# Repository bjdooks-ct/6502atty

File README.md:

# 6502 Atty

A 6502 SBC with an ATMega as a contoller and monitor for the 6502.

This is an initial commit as PCBs are off for manufacture and not been tested. This includes the prototype firmware and the first cut of the firmware code.

The ATmega is probably the easiest MCU to get and program which is 5V tolerant. The 1284P is the current choice as the smaller memory versions are not much cheaper.

There is now a [photo album](https://photos.app.goo.gl/qwDDgCh3WiyMoqd4A) of the build on my google photos.

The clock synchronisation logic is provided by U2A and U2B. U2B takes the PWM output from the ATMega and is used to both halve ti and make it a square wave. The /S input is used when the clock is high to stop any transition low (which would complete the 6502's cycle) which comes from the U2A flip-flop. U2A is triggered by an access to the ATMega and sets /CLOCK_STOP active to stop the 6502 clock until the /AT_ACK signal is active, resetting U2A and making /CLOCK_STOP inactive which then allows U2B to continue generating a clock for the 6502.

## Build notes for v1 rev1

- The 100UF capacitors are 16mm long so trying 47uF, layout change?

The LED resistors will probably need to be reduced to 680R or low as 506R depending on the LEDs being fitted.

The pull-up/pull-down resistors can be anywhere from 1K to 4K7, experiments with previous boards show 10K may not be suitable with certain variants of the 6052. Anything below 1K is probably going to have issues with current dissapation as that will be around 5mA per resistor. 

During test it was found that there seems to be a difference in operation dependong on how the PHi2 jumper is selected. If the PHI2O is used, we get proper operation but if CPU_CLK is seleted then the download code works but the code that is downloaded does not work.

## PCB updates (v1 rev2)

The updates for the second PCB revision are mostly bug-fixes and to make the board smaller to try and get to the 10x10cm point that JLCPCB and others use for cheaper services. There may be in future a version with a few bits of surface mount, like moving to one of the USB capable Atmel devices and adding a direct USB port.

- Added J12 to route ~WE signal to the PGM/~WE to allow SRAM
  - Also requires a R/!W signal gated with PHI2 high
  - Added R~{W}ph signal for ROM
  - This new signal could also drive RAM ~WE and connect ~CS to A15
- Connected ROM's VPP signal to GND, if using SRAM, ties A14 to GND
- U9C's pins 9 and 10 swapped for routing
- U11's E1/E2 pins swapped for easier routing
- Transcription error from prototype, ROM_ACC should be from AND not NAND gate
  - Swao U8C for one of U10 spare gates
- RDY line missing pull-up resistor
- 74LS573 replaced with 74LS574
  - 573 latches when Load is high, and our enable is low
  - 574 will load on rising edge of load pin, so should work
- Made PCB smaller, moved a few LEDs and things around to make this work
- Dropped 1K series drive resistor for the crystal
  - ATMega will not start if this resistor is there
- Serial converter is rotated 180deg to the actual unit
- Recomendation for AVRisp is to use 10K on ATMega's nRESET, so changed for now
  - See crystal series resistor notes.
- Added silkscreen with major part info to help with production

Currently unknown issues:
- Firmware only works with PHI2 jumper on PHI2out
  - can't see any scoped difference between CPUclk and PHI2out
  - possibly a rise-time on the clock with the 1K resistor in it

## PCB updates (v1 rev3)

This revision has minor updates for ease of assembly and a few minor annoyances over how the layout has come out, such as the mounting hole positions not being fully aligned.

The changes are:

- Made LEDs all the same orientation
  - also changed D2's resistor to be on ground side to make routing nicer
- Reduction in the x-size of the board by pushing control logic over
- Changed ROM A13 to solder pad, probably ok to just have A13 on this pin
- Used per-pin options on DIP to remove automatic ground ties
  - manually added a single ground tie to those pads
  - also made the keep-out a bit bigger to allow easier isolation cuts
- Made hole positions mostly consistent at edge of board
- Got down to 100x100mm dimensions with a more shuffling
- Added header and resistors for last two LEDs on bargrapth
  - Hesader J13 and two resistors to VCC for these
- Replaced input buffer U5 with 74x574
  - Added IOCLK from PHI2
  - Removed R26 as not needed
- could we use a 74x574 as input buffer too
  - if we tied ~OE and CP this would almost work, FF loaded on low-high
  - decided to bring PHI2 to the 74x574 to load state before read
  - device latches on low high and we need stable during the high clock phase
- Minor updats to clearand and island removal on the power planes

Processed the files and sent to JLCPCB, the manufacturing files commited in kicad/release3

To do for rev4:
- do we really need to have pull-ups on nmi/irq lines
  - atmega is always going to be needed unless you inject clk into gates

# Firmware

The firmware is currently in development. To build, you will need at-least avr-gcc and the relevant libraries and is currently only being tested on Linux (Debian). Once built, download to the ATMega using something like avrdude.

## Revision information

The original prototype version was built on a perfboard, and not released.

# Notes

Bee logo provided by Rob Kendrick

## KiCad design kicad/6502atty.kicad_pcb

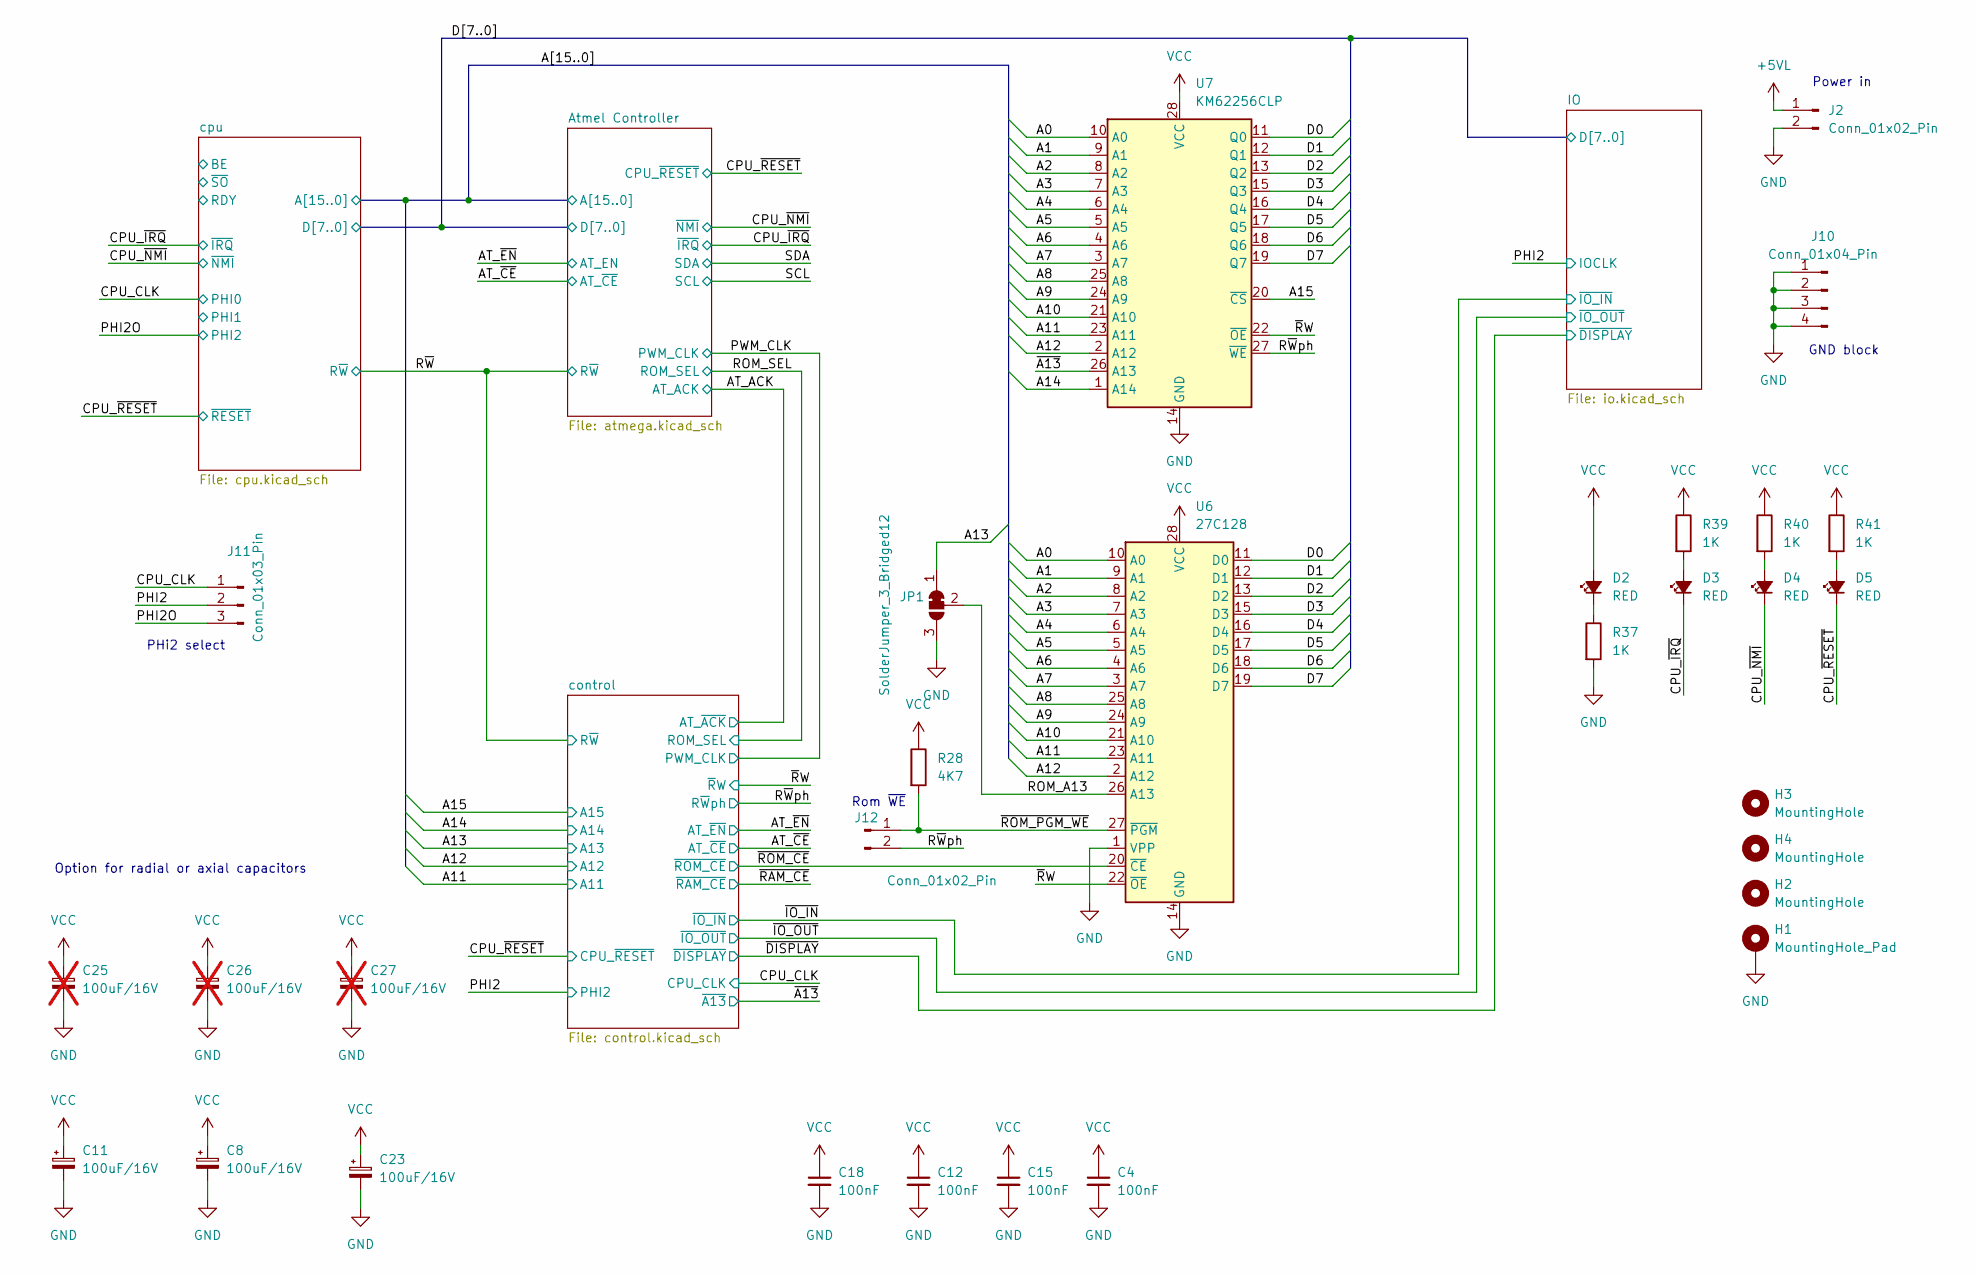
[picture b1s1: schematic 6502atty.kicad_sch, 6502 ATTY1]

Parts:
C4, C12, C15, C18: 100nF; C_Disc_D4.3mm_W1.9mm_P5.00mm
C8, C11, C23: 100uF/16V; CP_Axial_L10.0mm_D6.0mm_P15.00mm_Horizontal
C25, C26, C27: 100uF/16V; CP_Radial_D6.3mm_P2.50mm; not fitted
D2, D3, D4, D5: RED; LED_D5.0mm
H1: MountingHole_Pad; MountingHole_3.2mm_M3_Pad
H2, H3, H4: MountingHole; MountingHole_3.2mm_M3_Pad
J2: Conn_01x02_Pin; Molex_KK-254_AE-6410-02A_1x02_P2.54mm_Vertical
J10: Conn_01x04_Pin; PinHeader_1x04_P2.54mm_Vertical
J11: Conn_01x03_Pin; PinHeader_1x03_P2.54mm_Vertical
J12: Conn_01x02_Pin; PinHeader_1x02_P2.54mm_Vertical
JP1: SolderJumper_3_Bridged12; SolderJumper-3_P1.3mm_Bridged12_Pad1.0x1.5mm_NumberLabels
R28: 4K7; R_Axial_DIN0207_L6.3mm_D2.5mm_P10.16mm_Horizontal
R37, R39, R40: 1K; R_Axial_DIN0207_L6.3mm_D2.5mm_P10.16mm_Horizontal
R41: 1K; R_Axial_DIN0207_L6.3mm_D2.5mm_P2.54mm_Vertical
U6: 27C128; DIP-28_W15.24mm
U7: KM62256CLP; DIP-28_W15.24mm

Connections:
+5VL: J2.1; also elsewhere on the board
/A0: U6.10 (A0), U7.10 (A0); also elsewhere on the board
/A1: U6.9 (A1), U7.9 (A1); also elsewhere on the board
/A2: U6.8 (A2), U7.8 (A2); also elsewhere on the board
/A3: U6.7 (A3), U7.7 (A3); also elsewhere on the board
/A4: U6.6 (A4), U7.6 (A4); also elsewhere on the board
/A5: U6.5 (A5), U7.5 (A5); also elsewhere on the board
/A6: U6.4 (A6), U7.4 (A6); also elsewhere on the board
/A7: U6.3 (A7), U7.3 (A7); also elsewhere on the board
/A8: U6.25 (A8), U7.25 (A8); also elsewhere on the board
/A9: U6.24 (A9), U7.24 (A9); also elsewhere on the board
/A10: U6.21 (A10), U7.21 (A10); also elsewhere on the board
/A11: U6.23 (A11), U7.23 (A11); also elsewhere on the board
/A12: U6.2 (A12), U7.2 (A12); also elsewhere on the board
/A13: JP1.1 (A); also elsewhere on the board
/A14: U7.1 (A14); also elsewhere on the board
/A15: U7.20 (~CS); also elsewhere on the board
/CPU_CLK: J11.1; also elsewhere on the board
/CPU_~IRQ: D3.1 (K); also elsewhere on the board
/CPU_~NMI: D4.1 (K); also elsewhere on the board
/CPU_~RESET: D5.1 (K); also elsewhere on the board
/D0: U6.11 (D0), U7.11 (Q0); also elsewhere on the board
/D1: U6.12 (D1), U7.12 (Q1); also elsewhere on the board
/D2: U6.13 (D2), U7.13 (Q2); also elsewhere on the board
/D3: U6.15 (D3), U7.15 (Q3); also elsewhere on the board
/D4: U6.16 (D4), U7.16 (Q4); also elsewhere on the board
/D5: U6.17 (D5), U7.17 (Q5); also elsewhere on the board
/D6: U6.18 (D6), U7.18 (Q6); also elsewhere on the board
/D7: U6.19 (D7), U7.19 (Q7); also elsewhere on the board
/PHI2: J11.2; also elsewhere on the board
/PHI2O: J11.3; also elsewhere on the board
/ROM_A13: JP1.2 (C), U6.26 (A13)
/R~Wph: J12.2, U7.27 (~WE); also elsewhere on the board
/~A13: U7.26 (A13); also elsewhere on the board
/~ROM_CE: U6.20 (~CE); also elsewhere on the board
/~ROM_PGM_WE: J12.1, R28.2, U6.27 (~PGM)
/~RW: U6.22 (~OE), U7.22 (~OE); also elsewhere on the board
GND: C4.2, C8.2, C11.2, C12.2, C15.2, C18.2, C23.2, C25.2, C26.2, C27.2, H1.1 (1_1), J2.2, J10.1, J10.2, J10.3, J10.4, JP1.3 (B), R37.2, U6.1 (VPP), U6.14 (GND), U7.14 (GND); also elsewhere on the board
unnamed: D2.1 (K), R37.1
unnamed: D3.2 (A), R39.2
unnamed: D4.2 (A), R40.2
unnamed: D5.2 (A), R41.2
VCC: C4.1, C8.1, C11.1, C12.1, C15.1, C18.1, C23.1, C25.1, C26.1, C27.1, D2.2 (A), R28.1, R39.1, R40.1, R41.1, U6.28 (VCC), U7.28 (VCC); also elsewhere on the board

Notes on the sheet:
Power in
GND block
Option for radial or axial capacitors
PHi2 select
Rom ~{WE}

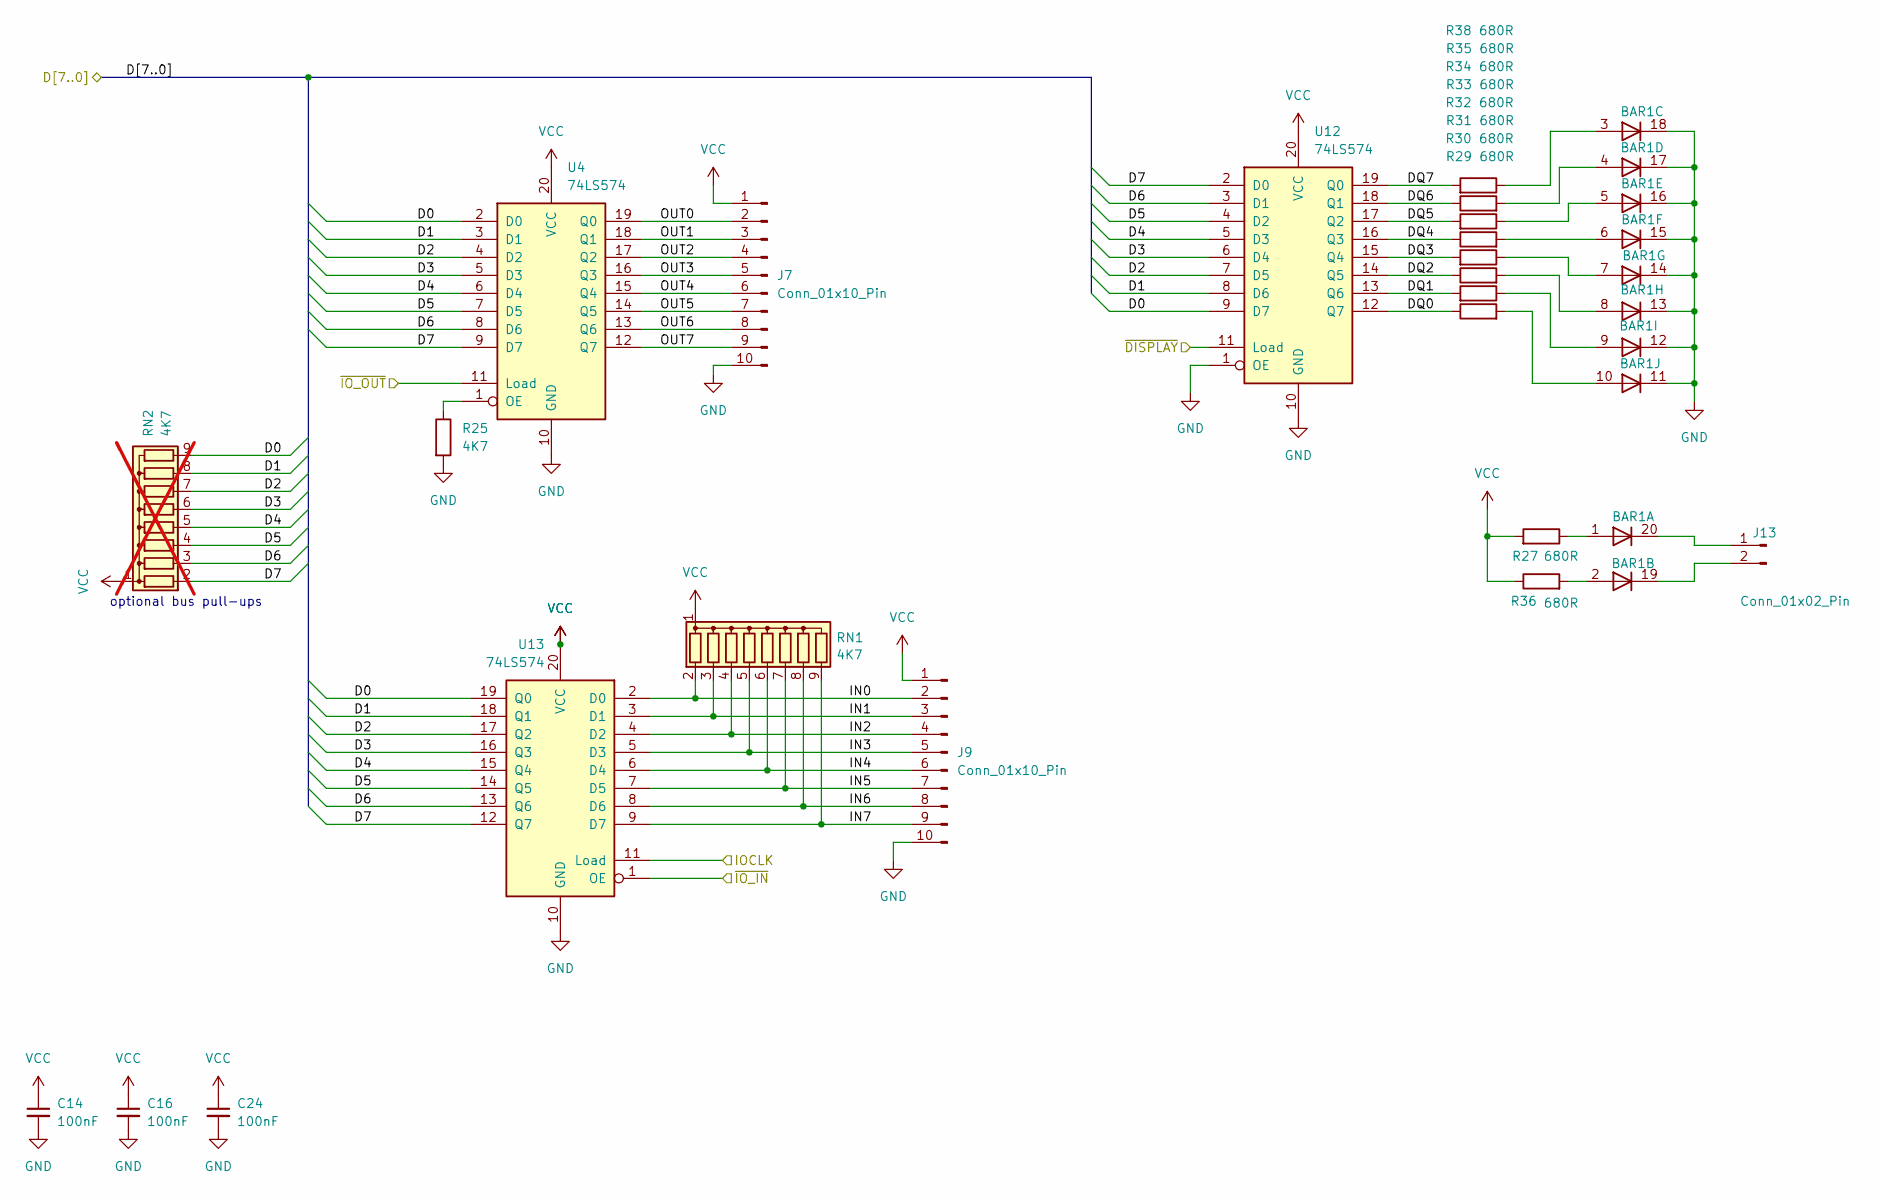
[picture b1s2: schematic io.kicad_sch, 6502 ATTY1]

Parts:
BAR1: HDSP-4850
C14, C16, C24: 100nF; C_Disc_D4.3mm_W1.9mm_P5.00mm
J7, J9: Conn_01x10_Pin; PinHeader_1x10_P2.54mm_Vertical
J13: Conn_01x02_Pin; PinHeader_1x02_P2.54mm_Vertical
R25: 4K7; R_Axial_DIN0207_L6.3mm_D2.5mm_P10.16mm_Horizontal
R27, R29, R30, R31, R32, R33, R34, R35, R36, R38: 680R; R_Axial_DIN0207_L6.3mm_D2.5mm_P2.54mm_Vertical
RN1: 4K7; R_Array_SIP9
RN2: 4K7; R_Array_SIP9; not fitted
U4, U12, U13: 74LS574; DIP-20_W7.62mm

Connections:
/D0: RN2.9 (R8), U4.2 (D0), U12.9 (D7), U13.19 (Q0); also elsewhere on the board
/D1: RN2.8 (R7), U4.3 (D1), U12.8 (D6), U13.18 (Q1); also elsewhere on the board
/D2: RN2.7 (R6), U4.4 (D2), U12.7 (D5), U13.17 (Q2); also elsewhere on the board
/D3: RN2.6 (R5), U4.5 (D3), U12.6 (D4), U13.16 (Q3); also elsewhere on the board
/D4: RN2.5 (R4), U4.6 (D4), U12.5 (D3), U13.15 (Q4); also elsewhere on the board
/D5: RN2.4 (R3), U4.7 (D5), U12.4 (D2), U13.14 (Q5); also elsewhere on the board
/D6: RN2.3 (R2), U4.8 (D6), U12.3 (D1), U13.13 (Q6); also elsewhere on the board
/D7: RN2.2 (R1), U4.9 (D7), U12.2 (D0), U13.12 (Q7); also elsewhere on the board
/IO/DQ0: R29.1, U12.12 (Q7)
/IO/DQ1: R30.2, U12.13 (Q6)
/IO/DQ2: R31.1, U12.14 (Q5)
/IO/DQ3: R32.2, U12.15 (Q4)
/IO/DQ4: R33.1, U12.16 (Q3)
/IO/DQ5: R34.2, U12.17 (Q2)
/IO/DQ6: R35.1, U12.18 (Q1)
/IO/DQ7: R38.2, U12.19 (Q0)
/IO/IN0: J9.2, RN1.2 (R1), U13.2 (D0)
/IO/IN1: J9.3, RN1.3 (R2), U13.3 (D1)
/IO/IN2: J9.4, RN1.4 (R3), U13.4 (D2)
/IO/IN3: J9.5, RN1.5 (R4), U13.5 (D3)
/IO/IN4: J9.6, RN1.6 (R5), U13.6 (D4)
/IO/IN5: J9.7, RN1.7 (R6), U13.7 (D5)
/IO/IN6: J9.8, RN1.8 (R7), U13.8 (D6)
/IO/IN7: J9.9, RN1.9 (R8), U13.9 (D7)
/IO/OUT0: J7.2, U4.19 (Q0)
/IO/OUT1: J7.3, U4.18 (Q1)
/IO/OUT2: J7.4, U4.17 (Q2)
/IO/OUT3: J7.5, U4.16 (Q3)
/IO/OUT4: J7.6, U4.15 (Q4)
/IO/OUT5: J7.7, U4.14 (Q5)
/IO/OUT6: J7.8, U4.13 (Q6)
/IO/OUT7: J7.9, U4.12 (Q7)
/PHI2: U13.11 (Load); also elsewhere on the board
/~DISPLAY: U12.11 (Load); also elsewhere on the board
/~IO_IN: U13.1 (OE); also elsewhere on the board
/~IO_OUT: U4.11 (Load); also elsewhere on the board
GND: BAR1.11 (K), BAR1.12 (K), BAR1.13 (K), BAR1.14 (K), BAR1.15 (K), BAR1.16 (K), BAR1.17 (K), BAR1.18 (K), C14.2, C16.2, C24.2, J7.10, J9.10, R25.2, U4.10 (GND), U12.1 (OE), U12.10 (GND), U13.10 (GND); also elsewhere on the board
unnamed: BAR1.1 (A), R27.1
unnamed: BAR1.20 (K), J13.1
unnamed: BAR1.2 (A), R36.2
unnamed: BAR1.19 (K), J13.2
unnamed: BAR1.3 (A), R38.1
unnamed: BAR1.4 (A), R35.2
unnamed: BAR1.5 (A), R34.1
unnamed: BAR1.6 (A), R33.2
unnamed: BAR1.7 (A), R32.1
unnamed: BAR1.8 (A), R31.2
unnamed: BAR1.9 (A), R30.1
unnamed: BAR1.10 (A), R29.2
unnamed: R25.1, U4.1 (OE)
VCC: C14.1, C16.1, C24.1, J7.1, J9.1, R27.2, R36.1, RN1.1 (common), RN2.1 (common), U4.20 (VCC), U12.20 (VCC), U13.20 (VCC); also elsewhere on the board

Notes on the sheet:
optional bus pull-ups

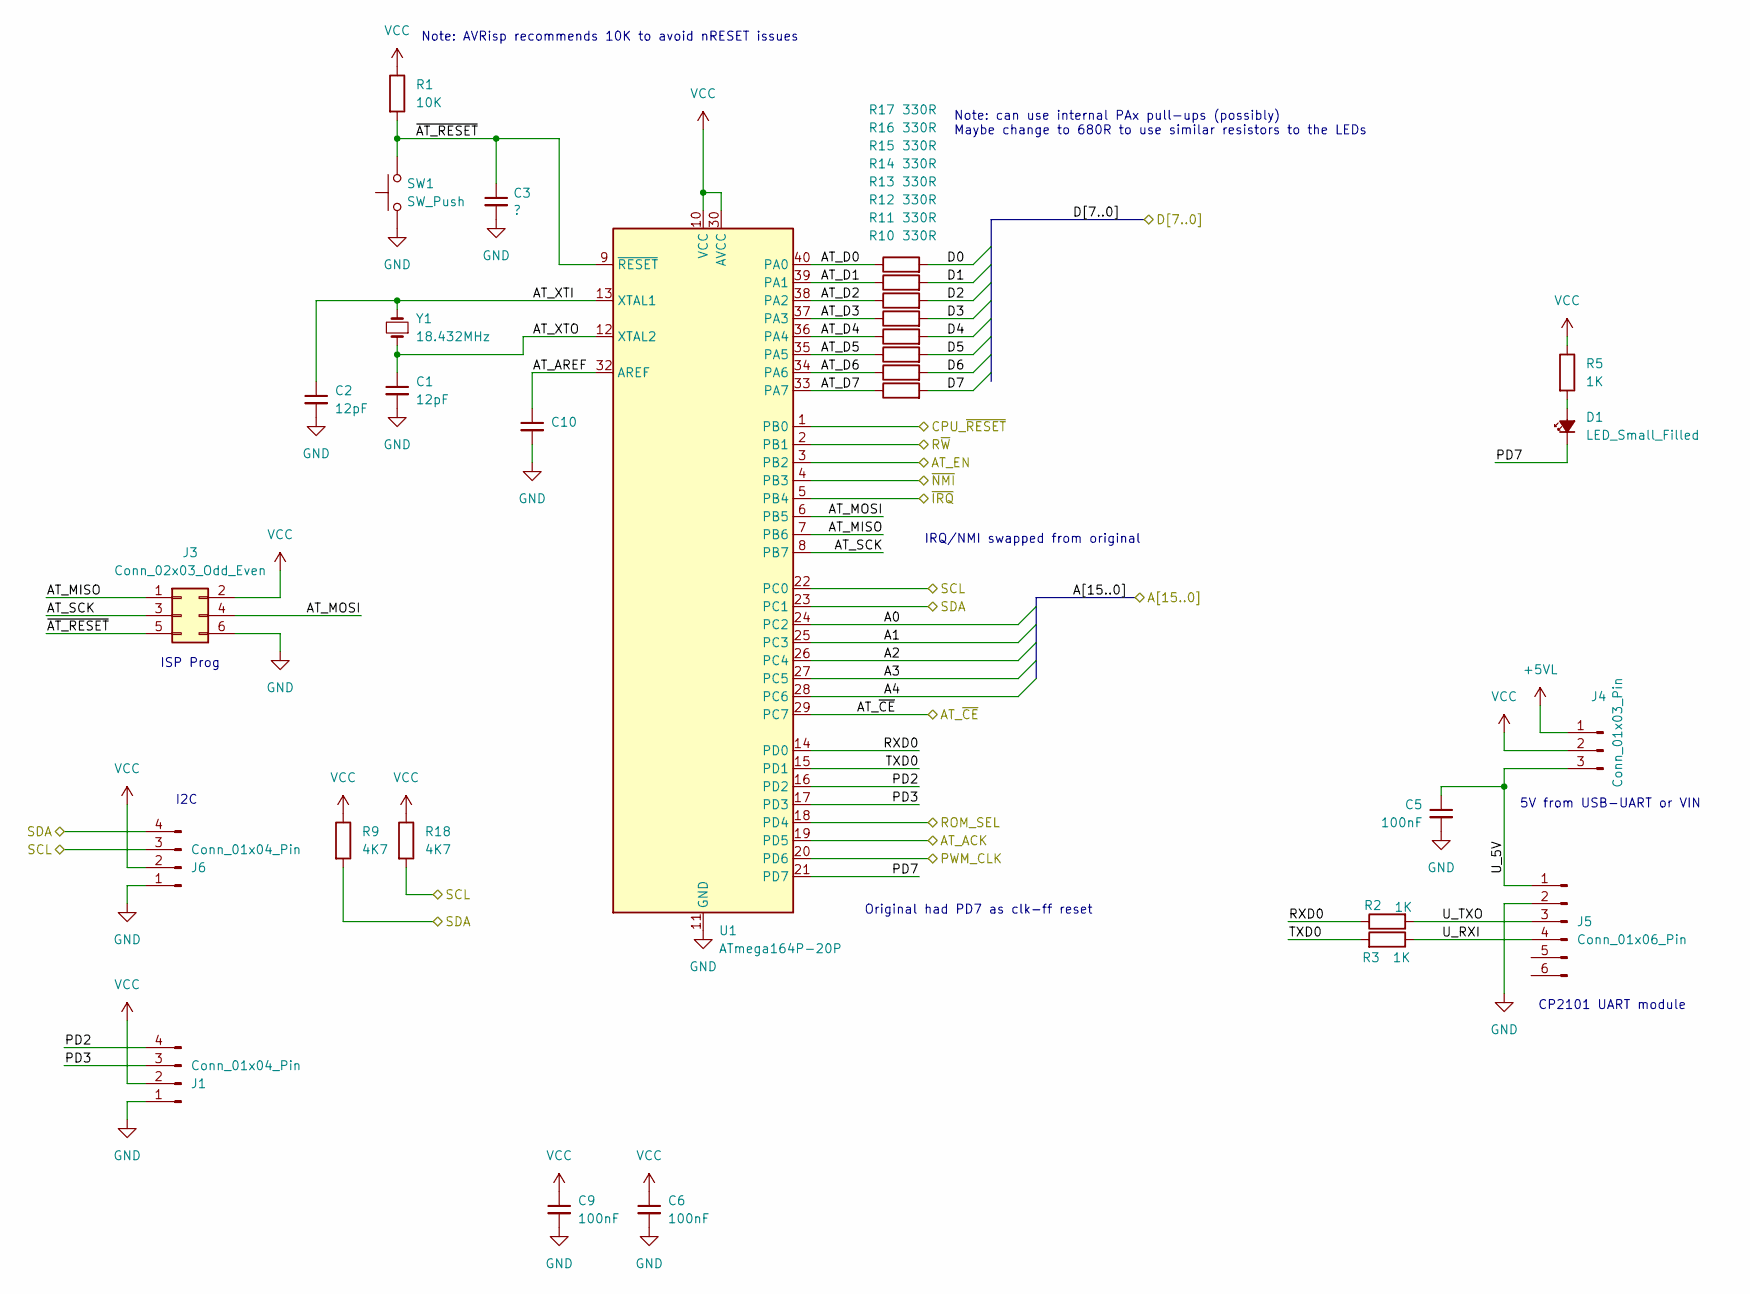
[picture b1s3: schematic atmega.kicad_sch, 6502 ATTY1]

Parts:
C1, C2: 12pF; C_Disc_D3.4mm_W2.1mm_P2.50mm
C3: ?; C_Disc_D3.4mm_W2.1mm_P2.50mm
C5, C6, C9: 100nF; C_Disc_D4.3mm_W1.9mm_P5.00mm
C10: C_Disc_D4.3mm_W1.9mm_P5.00mm
D1: LED_Small_Filled; LED_D5.0mm
J1: Conn_01x04_Pin; PinHeader_1x04_P2.54mm_Vertical
J3: Conn_02x03_Odd_Even; PinHeader_2x03_P2.54mm_Vertical
J4: Conn_01x03_Pin; PinHeader_1x03_P2.54mm_Vertical
J5: Conn_01x06_Pin; PinHeader_1x06_P2.54mm_Vertical
J6: Conn_01x04_Pin; PinSocket_1x04_P2.54mm_Vertical
R1: 10K; R_Axial_DIN0207_L6.3mm_D2.5mm_P2.54mm_Vertical
R2, R3: 1K; R_Axial_DIN0207_L6.3mm_D2.5mm_P10.16mm_Horizontal
R5: 1K; R_Axial_DIN0207_L6.3mm_D2.5mm_P2.54mm_Vertical
R9, R18: 4K7; R_Axial_DIN0207_L6.3mm_D2.5mm_P10.16mm_Horizontal
R10, R11, R12, R13, R14, R15, R16, R17: 330R; R_Axial_DIN0207_L6.3mm_D2.5mm_P10.16mm_Horizontal
SW1: SW_Push; SW_TH_Tactile_Omron_B3F-10xx
U1: ATmega164P-20P; DIP-40_W15.24mm
Y1: 18.432MHz; Crystal_HC49-4H_Vertical

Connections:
+5VL: J4.1; also elsewhere on the board
/A0: U1.24 (PC2); also elsewhere on the board
/A1: U1.25 (PC3); also elsewhere on the board
/A2: U1.26 (PC4); also elsewhere on the board
/A3: U1.27 (PC5); also elsewhere on the board
/A4: U1.28 (PC6); also elsewhere on the board
/AT_ACK: U1.19 (PD5); also elsewhere on the board
/AT_~CE: U1.29 (PC7); also elsewhere on the board
/AT_~EN: U1.3 (PB2); also elsewhere on the board
/Atmel Controller/AT_AREF: C10.1, U1.32 (AREF)
/Atmel Controller/AT_D0: R17.1, U1.40 (PA0)
/Atmel Controller/AT_D1: R16.1, U1.39 (PA1)
/Atmel Controller/AT_D2: R15.1, U1.38 (PA2)
/Atmel Controller/AT_D3: R14.1, U1.37 (PA3)
/Atmel Controller/AT_D4: R13.1, U1.36 (PA4)
/Atmel Controller/AT_D5: R12.1, U1.35 (PA5)
/Atmel Controller/AT_D6: R11.1, U1.34 (PA6)
/Atmel Controller/AT_D7: R10.1, U1.33 (PA7)
/Atmel Controller/AT_MISO: J3.1, U1.7 (PB6)
/Atmel Controller/AT_MOSI: J3.4, U1.6 (PB5)
/Atmel Controller/AT_SCK: J3.3, U1.8 (PB7)
/Atmel Controller/AT_XTI: C2.1, U1.13 (XTAL1), Y1.2
/Atmel Controller/AT_XTO: C1.1, U1.12 (XTAL2), Y1.1
/Atmel Controller/PD2: J1.4, U1.16 (PD2)
/Atmel Controller/PD3: J1.3, U1.17 (PD3)
/Atmel Controller/PD7: D1.1 (K), U1.21 (PD7)
/Atmel Controller/RXD0: R2.1, U1.14 (PD0)
/Atmel Controller/TXD0: R3.2, U1.15 (PD1)
/Atmel Controller/U_5V: C5.1, J4.3, J5.1
/Atmel Controller/U_RXI: J5.4, R3.1
/Atmel Controller/U_TXO: J5.3, R2.2
/Atmel Controller/~AT_RESET: C3.1, J3.5, R1.2, SW1.2, U1.9 (~RESET)
/CPU_~IRQ: U1.5 (PB4); also elsewhere on the board
/CPU_~NMI: U1.4 (PB3); also elsewhere on the board
/CPU_~RESET: U1.1 (PB0); also elsewhere on the board
/D0: R17.2; also elsewhere on the board
/D1: R16.2; also elsewhere on the board
/D2: R15.2; also elsewhere on the board
/D3: R14.2; also elsewhere on the board
/D4: R13.2; also elsewhere on the board
/D5: R12.2; also elsewhere on the board
/D6: R11.2; also elsewhere on the board
/D7: R10.2; also elsewhere on the board
/PWM_CLK: U1.20 (PD6); also elsewhere on the board
/ROM_SEL: U1.18 (PD4); also elsewhere on the board
/R~W: U1.2 (PB1); also elsewhere on the board
/SCL: J6.3, R18.2, U1.22 (PC0)
/SDA: J6.4, R9.2, U1.23 (PC1)
GND: C1.2, C2.2, C3.2, C5.2, C6.2, C9.2, C10.2, J1.1, J3.6, J5.2, J6.1, SW1.1, U1.11 (GND), U1.31 (GND); also elsewhere on the board
unnamed: D1.2 (A), R5.2
VCC: C6.1, C9.1, J1.2, J3.2, J4.2, J6.2, R1.1, R5.1, R9.1, R18.1, U1.10 (VCC), U1.30 (AVCC); also elsewhere on the board

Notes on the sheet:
ISP Prog
I2C
5V from USB-UART or VIN
Original had PD7 as clk-ff reset
IRQ/NMI swapped from original
Note: can use internal PAx pull-ups (possibly) Maybe change to 680R to use similar resistors to the LEDs
CP2101 UART module
Note: AVRisp recommends 10K to avoid nRESET issues

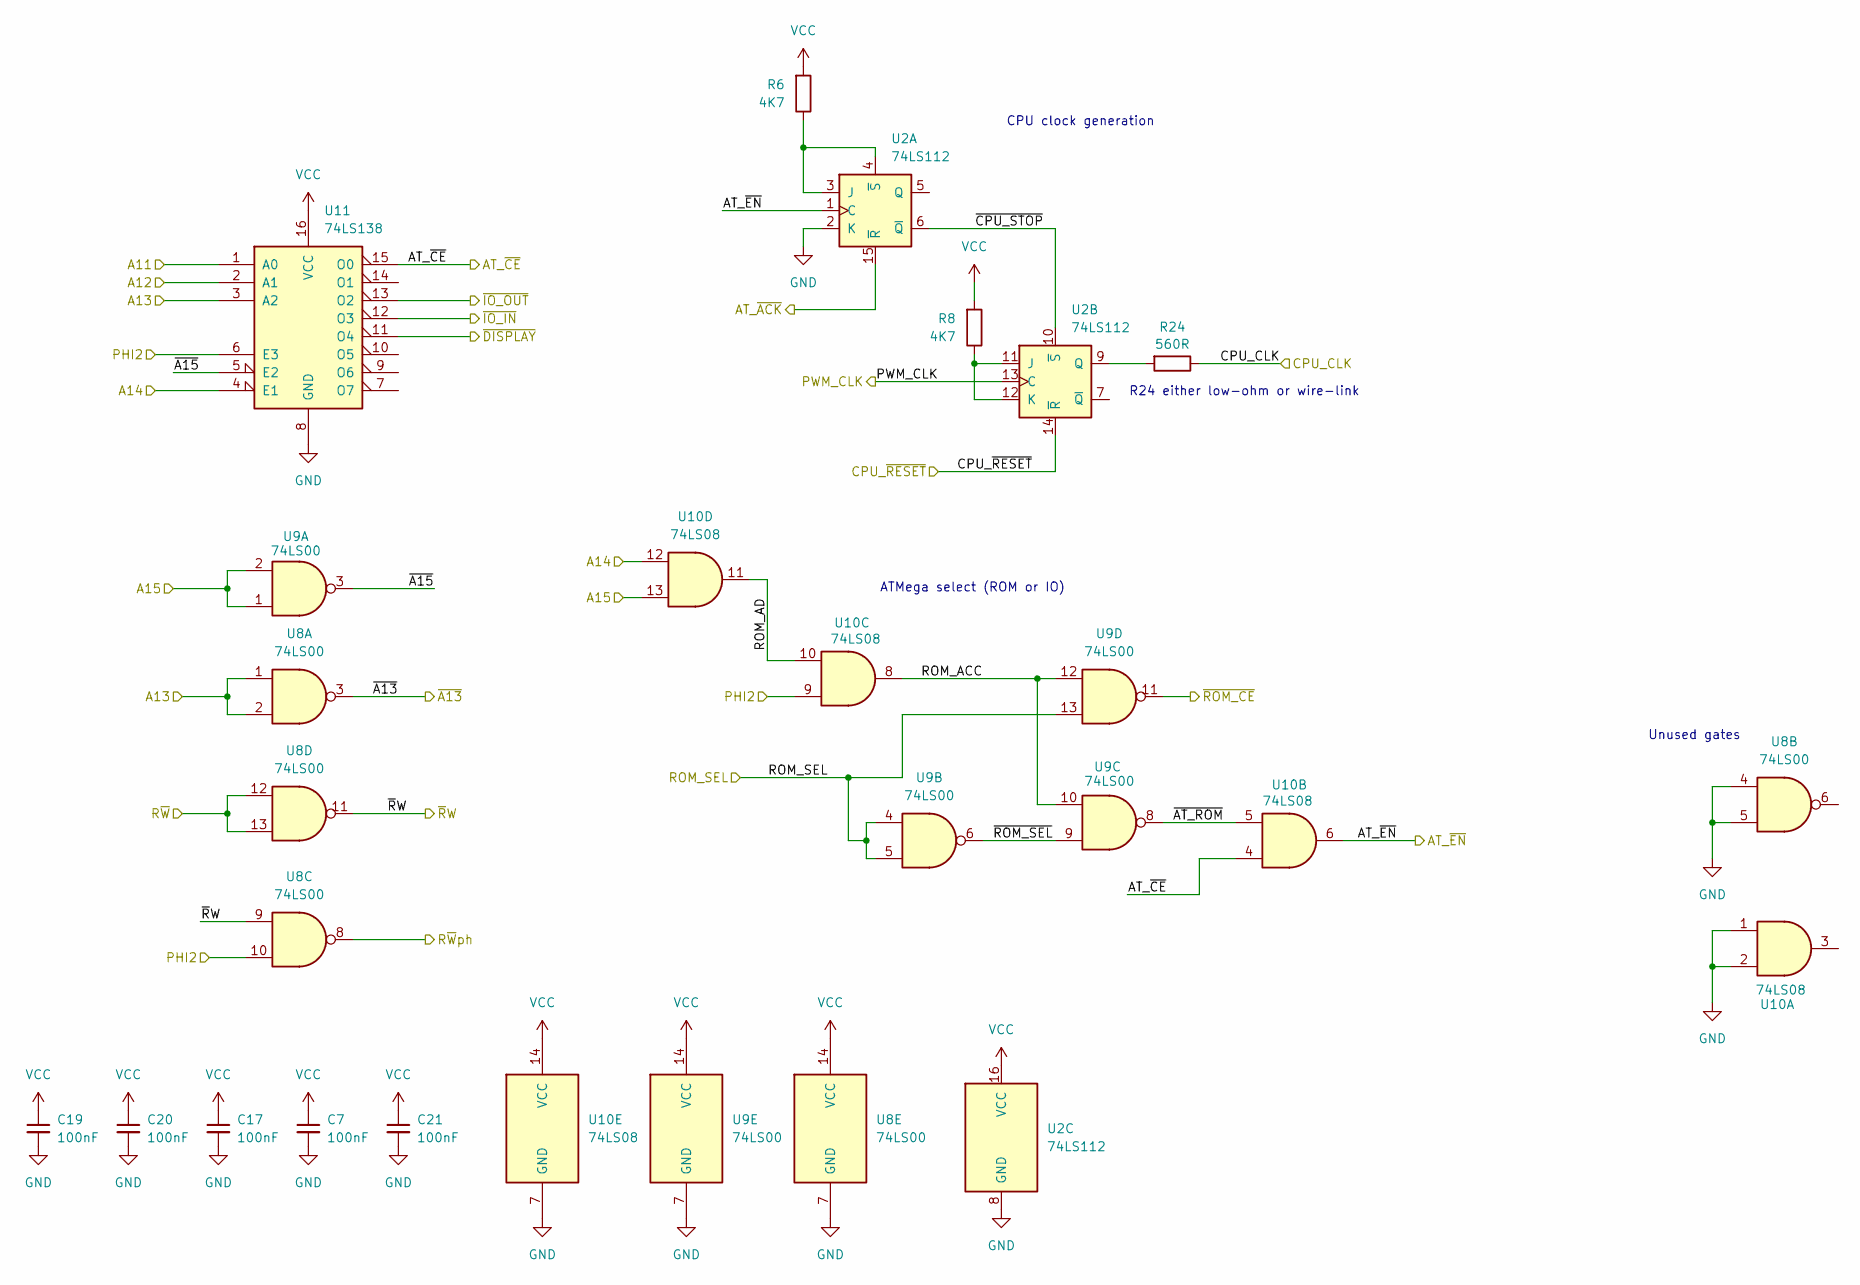
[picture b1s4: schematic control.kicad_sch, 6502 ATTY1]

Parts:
C7, C17, C19, C20, C21: 100nF; C_Disc_D4.3mm_W1.9mm_P5.00mm
R6, R8: 4K7; R_Axial_DIN0207_L6.3mm_D2.5mm_P10.16mm_Horizontal
R24: 560R; R_Axial_DIN0207_L6.3mm_D2.5mm_P10.16mm_Horizontal
U2: 74LS112; DIP-16_W7.62mm
U8, U9: 74LS00; DIP-14_W7.62mm
U10: 74LS08; DIP-14_W7.62mm
U11: 74LS138; DIP-16_W7.62mm

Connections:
/A11: U11.1 (A0); also elsewhere on the board
/A12: U11.2 (A1); also elsewhere on the board
/A13: U8.1, U8.2, U11.3 (A2); also elsewhere on the board
/A14: U10.12, U11.4 (E1); also elsewhere on the board
/A15: U9.1, U9.2, U10.13; also elsewhere on the board
/AT_ACK: U2.15 (~R); also elsewhere on the board
/AT_~CE: U10.4, U11.15 (O0); also elsewhere on the board
/AT_~EN: U2.1 (C), U10.6; also elsewhere on the board
/CPU_CLK: R24.1; also elsewhere on the board
/CPU_~RESET: U2.14 (~R); also elsewhere on the board
/PHI2: U8.10, U10.9, U11.6 (E3); also elsewhere on the board
/PWM_CLK: U2.13 (C); also elsewhere on the board
/ROM_SEL: U9.4, U9.5, U9.13; also elsewhere on the board
/R~W: U8.12, U8.13; also elsewhere on the board
/R~Wph: U8.8; also elsewhere on the board
/control/ROM_ACC: U9.10, U9.12, U10.8
/control/ROM_AD: U10.10, U10.11
/control/~A15: U9.3, U11.5 (E2)
/control/~AT_ROM: U9.8, U10.5
/control/~CPU_STOP: U2.6 (~Q), U2.10 (~S)
/control/~ROM_SEL: U9.6, U9.9
/~A13: U8.3; also elsewhere on the board
/~DISPLAY: U11.11 (O4); also elsewhere on the board
/~IO_IN: U11.12 (O3); also elsewhere on the board
/~IO_OUT: U11.13 (O2); also elsewhere on the board
/~ROM_CE: U9.11; also elsewhere on the board
/~RW: U8.9, U8.11; also elsewhere on the board
GND: C7.2, C17.2, C19.2, C20.2, C21.2, U2.2 (K), U2.8 (GND), U8.4, U8.5, U8.7 (GND), U9.7 (GND), U10.1, U10.2, U10.7 (GND), U11.8 (GND); also elsewhere on the board
unnamed: R6.1, U2.3 (J), U2.4 (~S)
unnamed: R8.1, U2.11 (J), U2.12 (K)
unnamed: R24.2, U2.9 (Q)
VCC: C7.1, C17.1, C19.1, C20.1, C21.1, R6.2, R8.2, U2.16 (VCC), U8.14 (VCC), U9.14 (VCC), U10.14 (VCC), U11.16 (VCC); also elsewhere on the board

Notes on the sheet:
R24 either low-ohm or wire-link
ATMega select (ROM or IO)
Unused gates
CPU clock generation

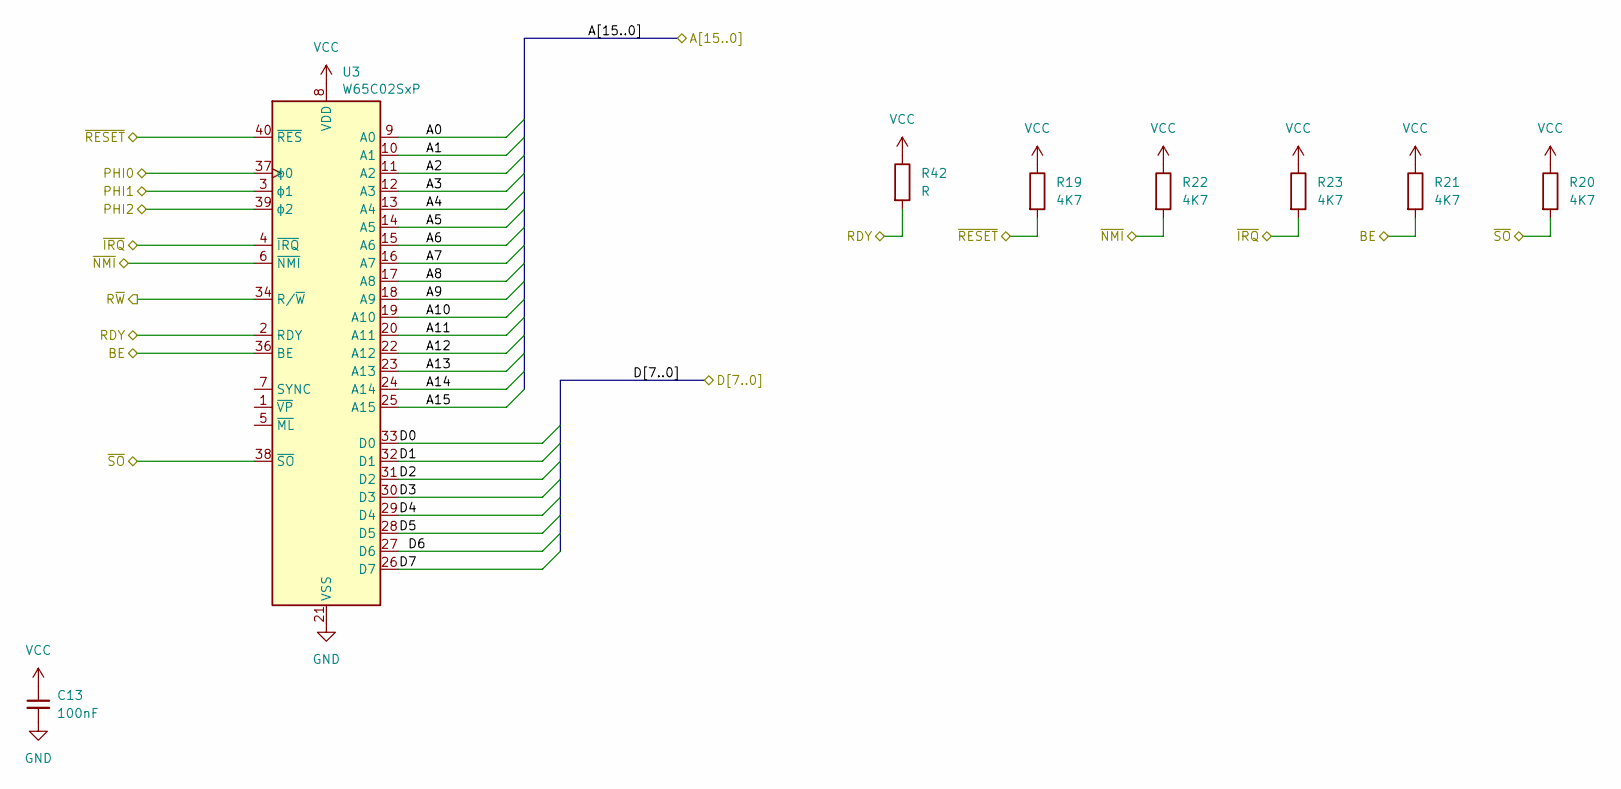
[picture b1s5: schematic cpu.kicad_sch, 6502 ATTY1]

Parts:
C13: 100nF; C_Disc_D4.3mm_W1.9mm_P5.00mm
R19, R20, R21, R22, R23: 4K7; R_Axial_DIN0207_L6.3mm_D2.5mm_P10.16mm_Horizontal
R42: R; R_Axial_DIN0207_L6.3mm_D2.5mm_P10.16mm_Horizontal
U3: W65C02SxP; DIP-40_W15.24mm

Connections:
/A0: U3.9 (A0); also elsewhere on the board
/A1: U3.10 (A1); also elsewhere on the board
/A2: U3.11 (A2); also elsewhere on the board
/A3: U3.12 (A3); also elsewhere on the board
/A4: U3.13 (A4); also elsewhere on the board
/A5: U3.14 (A5); also elsewhere on the board
/A6: U3.15 (A6); also elsewhere on the board
/A7: U3.16 (A7); also elsewhere on the board
/A8: U3.17 (A8); also elsewhere on the board
/A9: U3.18 (A9); also elsewhere on the board
/A10: U3.19 (A10); also elsewhere on the board
/A11: U3.20 (A11); also elsewhere on the board
/A12: U3.22 (A12); also elsewhere on the board
/A13: U3.23 (A13); also elsewhere on the board
/A14: U3.24 (A14); also elsewhere on the board
/A15: U3.25 (A15); also elsewhere on the board
/CPU_CLK: U3.37 (ϕ0); also elsewhere on the board
/CPU_~IRQ: R23.2, U3.4 (~IRQ); also elsewhere on the board
/CPU_~NMI: R22.2, U3.6 (~NMI); also elsewhere on the board
/CPU_~RESET: R19.2, U3.40 (~RES); also elsewhere on the board
/D0: U3.33 (D0); also elsewhere on the board
/D1: U3.32 (D1); also elsewhere on the board
/D2: U3.31 (D2); also elsewhere on the board
/D3: U3.30 (D3); also elsewhere on the board
/D4: U3.29 (D4); also elsewhere on the board
/D5: U3.28 (D5); also elsewhere on the board
/D6: U3.27 (D6); also elsewhere on the board
/D7: U3.26 (D7); also elsewhere on the board
/PHI2O: U3.39 (ϕ2); also elsewhere on the board
/R~W: U3.34 (R/~W); also elsewhere on the board
/cpu/BE: R21.2, U3.36 (BE)
/cpu/PHI1: U3.3 (ϕ1)
/cpu/RDY: R42.2, U3.2 (RDY)
/cpu/~SO: R20.2, U3.38 (~SO)
GND: C13.2, U3.21 (VSS); also elsewhere on the board
VCC: C13.1, R19.1, R20.1, R21.1, R22.1, R23.1, R42.1, U3.8 (VDD); also elsewhere on the board

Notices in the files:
kicad/6502atty.kicad_pcb:
© 2025 BJ Dooks
kicad/6502atty.kicad_sch:
© 2025 Ben Dooks
